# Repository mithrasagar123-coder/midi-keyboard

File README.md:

# MIDI Keypad

## Overview

A custom MIDI keypad with switches, sliders, rotary encoders, neopixels and capacitive touch keys. You can connect it to a computer music software and make sick beats :) 

I designed this for my Week 3 project of halflife, a 10-week program where you can design and build hardware projects free of cost!

## Parts
* Bourns Slide Potentiometers: analog faders
* Kailh Choc Low-Profile Switches!
* SK6812 MINI-E Neopixels: Cool RGB lighting!
* EC11 Rotary Encoders: spinny spinny knob!
* Capacitive Touch Keys!
* Custom keycaps!

## Schematic

## Board

*(The small guy in the corner is Toya Aoyagi from Project Sekai. He plays piano.)*

## Custom Keycaps

Made with CAD. They're also music themed!

## BOM

| Item                            | Qty | Supplier   | Cost/item | Total Cost | link                                                                                                                                                                                                                                                                                                                                                                                                                                                                                                                                                                                                                                                                                                                                                                                     |
|---------------------------------|-----|------------|-----------|------------|------------------------------------------------------------------------------------------------------------------------------------------------------------------------------------------------------------------------------------------------------------------------------------------------------------------------------------------------------------------------------------------------------------------------------------------------------------------------------------------------------------------------------------------------------------------------------------------------------------------------------------------------------------------------------------------------------------------------------------------------------------------------------------------|
| PCB                             | 1   | JLCPCB     | $11.10    | $11.10     | https://cart.jlcpcb.com/quote?stencilLayer=2&stencilWidth=100&stencilLength=100&stencilCounts=5&plateType=1&spm=Jlcpcb.Homepage.1010                                                                                                                                                                                                                                                                                                                                                                                                                                                                                                                                                                                                                                                     |
| Waveshare ESP32-S3-Zero         | 1   | AliExpress | $1.73     | $1.73      | https://www.aliexpress.us/item/3256812546916539.html?src=google&snps=y&src=google&albch=shopping&acnt=708-803-3821&isdl=y&slnk=&plac=&mtctp=&albbt=Google_7_shopping&aff_platform=google&aff_short_key=UneMJZVf&gclsrc=aw.ds&albagn=888888&ds_e_adid=&ds_e_matchtype=&ds_e_device=c&ds_e_network=x&ds_e_product_group_id=&ds_e_product_id=en3256812546916539&ds_e_product_merchant_id=5640611728&ds_e_product_country=US&ds_e_product_language=en&ds_e_product_channel=online&ds_e_product_store_id=&ds_url_v=2&albcp=20542171667&albag=&isSmbAutoCall=false&needSmbHouyi=false&gad_source=1&gad_campaignid=18545443176&gbraid=0AAAAAD6I-hEB6dWLblooIA5PgnahOMbmg&gclid=CjwKCAjw0fbWBhBkEiwAwJuQ8d16zJPUf6k7zpfUHVgUOGvAry6US2Azt0_kuRLwZjQwV-wxgqL_6RoCK5QQAvD_BwE&gatewayAdapt=glo2usa |
| Bourns Slide Potentiometers     | 2   | AliExpress | $2.30     | $4.60      | https://www.aliexpress.us/item/3256809700464952.html?spm=a2g0o.productlist.main.11.161a4558EVDQQT&algo_pvid=1d934da7-1327-4768-a0c9-19a97e59dcba&algo_exp_id=1d934da7-1327-4768-a0c9-19a97e59dcba-10&pdp_ext_f=%7B%22order%22%3A%22198%22%2C%22eval%22%3A%221%22%2C%22fromPage%22%3A%22search%22%7D&pdp_npi=6%40dis%21USD%212.30%212.30%21%21%2115.28%2115.28%21%402101d9ef17929744528883176e0f0b%2112000050482313783%21sea%21US%218341090660%21ABX%211%210%21n_tag%3A-29910%3Bd%3A87101d9a%3Bm03_new_user%3A-29895&curPageLogUid=QnxnCdxkXP3u&utparam-url=scene%3Asearch%7Cquery_from%3A%7Cx_object_id%3A1005009886779704%7C_p_origin_prod%3A                                                                                                                                           |
| Kailh Choc Low-Profile Switches | 1   | AliExpress | $4.36     | $4.36      | https://www.aliexpress.us/item/3256812653947991.html?spm=a2g0o.productlist.main.5.46583c5f4cJJz8&algo_pvid=ebc10692-7dcd-47ba-b681-e56178b7efc4&algo_exp_id=ebc10692-7dcd-47ba-b681-e56178b7efc4-4&pdp_ext_f=%7B%22order%22%3A%2254%22%2C%22eval%22%3A%221%22%2C%22fromPage%22%3A%22search%22%7D&pdp_npi=6%40dis%21USD%214.36%211.09%21%21%214.36%211.09%21%402103119c17929747023374751e0eba%2112000059499320560%21sea%21US%218341090660%21ABX%211%210%21n_tag%3A-29910%3Bd%3A87101d9a%3Bm03_new_user%3A-29895%3BpisId%3A5000000218165390&curPageLogUid=EVQYU9kkAF7W&utparam-url=scene%3Asearch%7Cquery_from%3A%7Cx_object_id%3A1005012840262743%7C_p_origin_prod%3A                                                                                                                     |
| SK6812 MINI-E Neopixels         | 1   | AliExpress | $11.97    | $11.97     | https://www.aliexpress.us/item/3256805000200413.html?spm=a2g0o.productlist.main.13.4b4d677eCb1Q04&utparam-url=scene%3Asearch%7Cquery_from%3Apc_back_same_best%7Cx_object_id%3A1005005186515165%7C_p_origin_prod%3A&algo_pvid=e608ed36-8626-4c29-a3e0-378040c81751&algo_exp_id=e608ed36-8626-4c29-a3e0-378040c81751&pdp_ext_f=%7B%22order%22%3A%22269%22%2C%22fromPage%22%3A%22search%22%7D&pdp_npi=6%40dis%21USD%2111.97%217.97%21%21%2111.97%217.97%21%402103117b17929748357703751e1084%2112000032026120161%21sea%21US%218341090660%21ABX%211%210%21n_tag%3A-29910%3Bd%3A87101d9a%3Bm03_new_user%3A-29895%3BpisId%3A5000000218165391&gatewayAdapt=4itemAdapt                                                                                                                            |
| 3D Printed Keycaps               | 1   | Local 3D Printing | $5.00     | $5.00      | https://local3dprinting.com/quote/a5eac5c8c8ba773fa208777f8c0ee6c91632d497ccf72ea1                                                                                                                              |
| EC11 Rotary Encoders            | 1   | AliExpress | $1.59     | $1.59      | https://www.aliexpress.us/item/3256807457768762.html?spm=a2g0o.detail.0.0.75d5I4OTI4OTV3&mp=1&pdp_npi=6%40dis%21USD%21USD+1.59%21USD+1.59%21%21USD+1.59%21%21%21%4021030f4a17929798118182921e0d61%2112000041630839430%21ct%21US%218341090660%21%211%210%21&_gl=1*1y8e9g4*_gcl_aw*R0NMLjE3OTI5NzkwMjAuQ2p3S0NBancwZmJXQmhCa0Vpd0F3SnVROFdQVDFIU1EzY2NqUmpMQUg1TjBmLTcxMFBUWjZLTlZMU19RVUtyU1dUR0NodlljUHFILUd4b0NRRklRQXZEX0J3RQ..*_gcl_dc*R0NMLjE3OTI5NzU2NDEuQ2p3S0NBancwZmJXQmhCa0Vpd0F3SnVROGQxNnpKUFVmNms3enBmVUhWZ1VPR3ZBcnk2VVMyQXp0MF9rdVJMd1pqUXdWLXd4Z3FMXzZSb0NLNVFRQXZEX0J3RQ..*_gcl_au*ODkwMzgyODczLjE3OTE3NzUwMzY.*_ga*MTgxNzgzODk1OC4xNzkyOTczNzgy*_ga_VED1YSGNC7*czE3OTI5NzkwMjIkbzIkZzEkdDE3OTI5Nzk4MTEkajYwJGwwJGgw&gatewayAdapt=glo2usa                                |
| Estimated total shipping        |     |            |           | $7.69      |                                                                                                                                                                                                                                                                                                                                                                                                                                                                                                                                                                                                                                                                                                                                                                                          |
| Total                           |     |            |           | $48.04     |                                                                                                                                                                                                                                                                                                                                                                                                                                                                                                                                                                                                                                                                                                                                                                                          |

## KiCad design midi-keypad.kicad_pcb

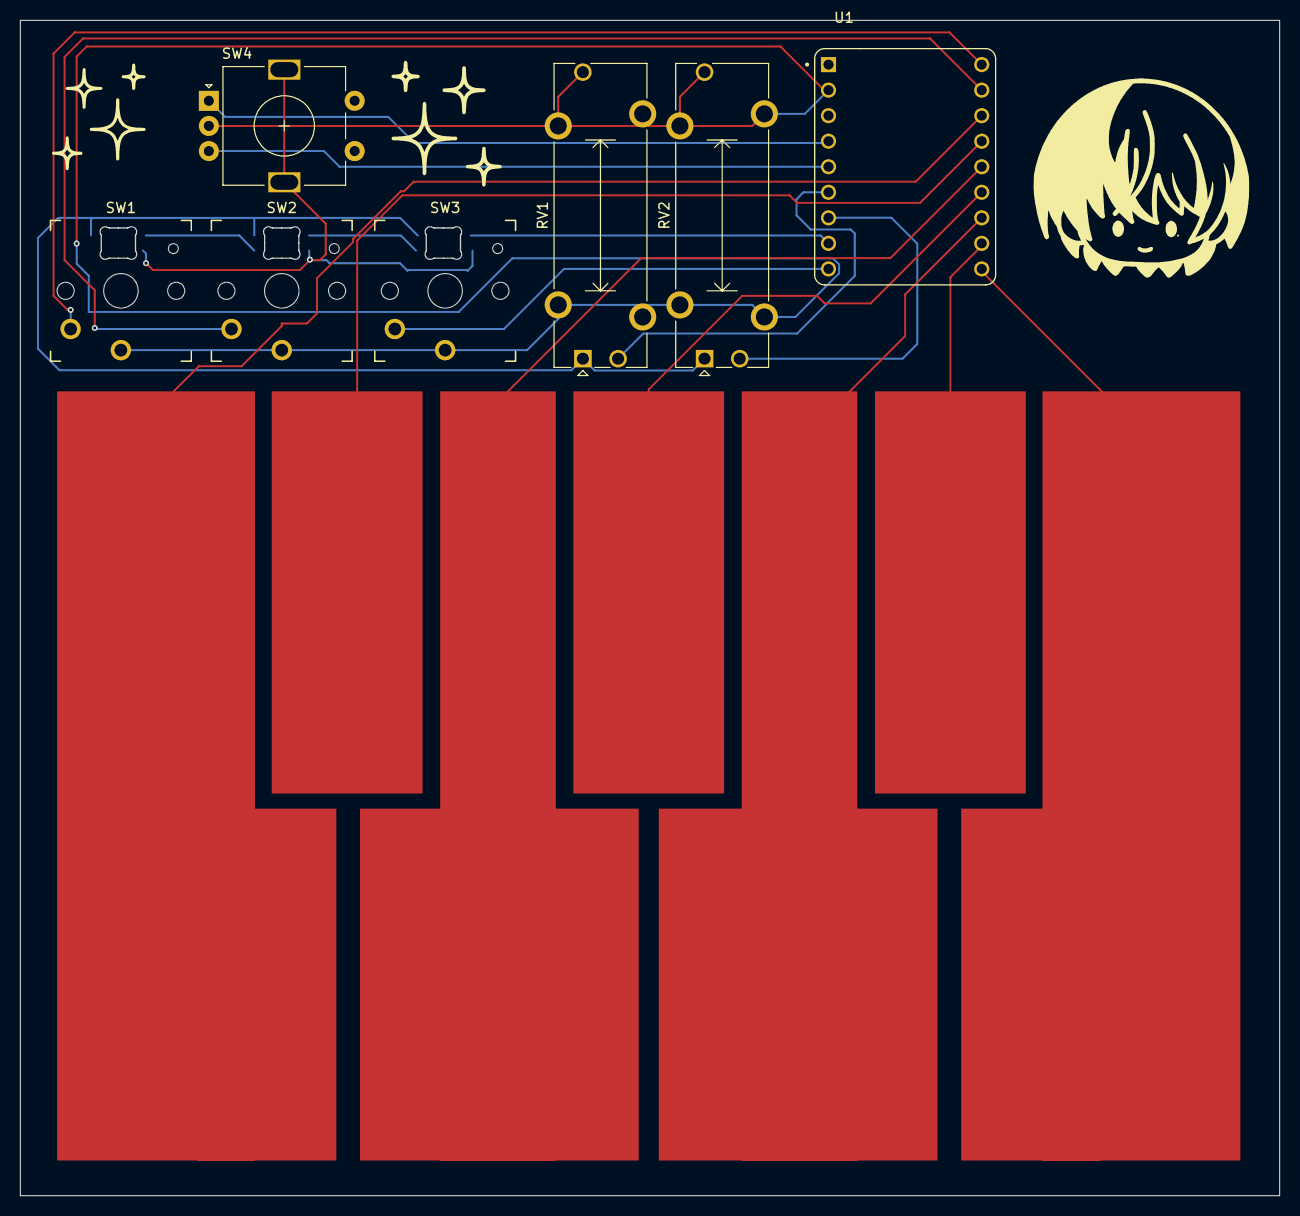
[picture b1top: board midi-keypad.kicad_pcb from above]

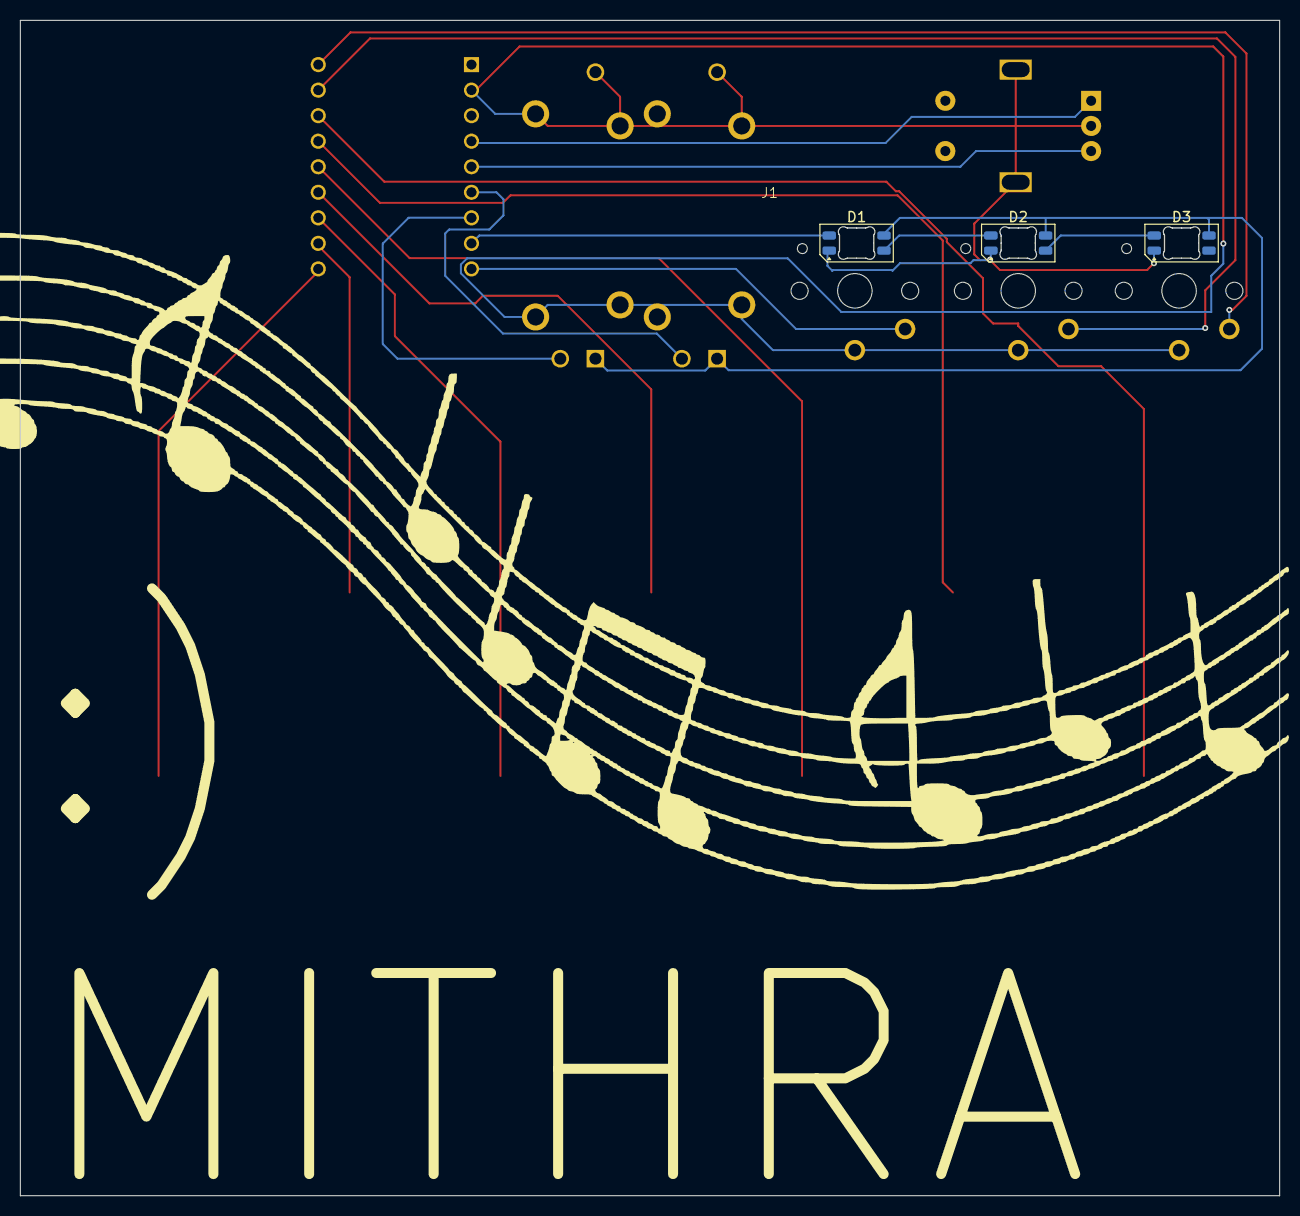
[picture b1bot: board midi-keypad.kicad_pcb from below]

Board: 2 copper layers, 125.2 x 116.9 mm, 11 parts (3 on the bottom side), 19 nets.

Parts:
D1, D2, D3: SK6812MINI-E; LED_SK6812MINI-E_3.2x2.8mm_P1.5mm_ReverseMount
J1: Capacitive Touch Buttons; Capacitive Keys
RV1, RV2: Slider; Potentiometer_Bourns_PTA1543_Single_Slide
SW1, SW2, SW3: SW_Push; Kailh Choc Low-Profile Switches
SW4: RotaryEncoder_Switch_MP; RotaryEncoder_Alps_EC11E-Switch_Vertical_H20mm
U1: Waveshare ESP32-S3-ZERO; Waveshare ESP32-S3-Zero

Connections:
+3.3V: D1.3 (VDD), D2.3 (VDD), D3.3 (VDD), RV1.1, RV2.1
/ENC1_A: SW4.A, U1.1 (GP1)
/ENC1_B: SW4.B, U1.2 (GP2)
/LED: D1.2 (DIN), U1.5 (GP5)
/SLIDE1: RV1.2, U1.3 (GP3)
/SLIDE2: RV2.2, U1.4 (GP4)
/SWITCH1: SW1.2, U1.TX
/SWITCH2: SW2.2, U1.RX
/SWITCH3: SW3.2, U1.6 (GP6)
/TOUCH1: J1.1, U1.13 (GP13)
/TOUCH2: J1.2, U1.12 (GP12)
/TOUCH3: J1.3, U1.11 (GP11)
/TOUCH4: J1.4, U1.10 (GP10)
/TOUCH5: J1.5, U1.9 (GP9)
/TOUCH6: J1.6, U1.8 (GP8)
/TOUCH7: J1.7, U1.7 (GP7)
GND: D1.1 (VSS), D2.1 (VSS), D3.1 (VSS), RV1.3, RV1.MP (MountPin), RV2.3, RV2.MP (MountPin), SW1.1, SW2.1, SW3.1, SW4.C, SW4.MP, U1.GND
unnamed: D1.4 (DOUT), D2.2 (DIN)
unnamed: D2.4 (DOUT), D3.2 (DIN)
